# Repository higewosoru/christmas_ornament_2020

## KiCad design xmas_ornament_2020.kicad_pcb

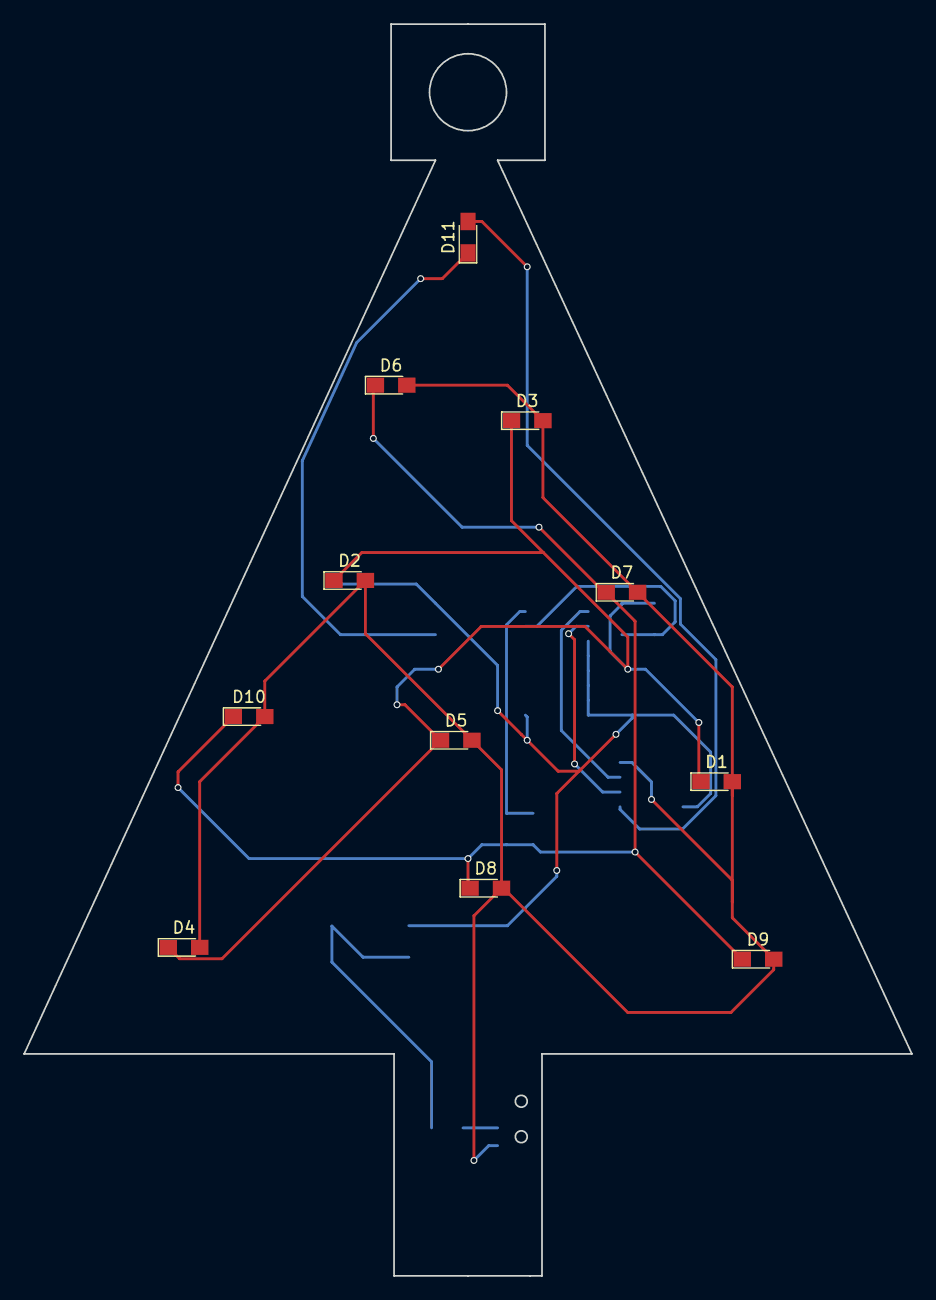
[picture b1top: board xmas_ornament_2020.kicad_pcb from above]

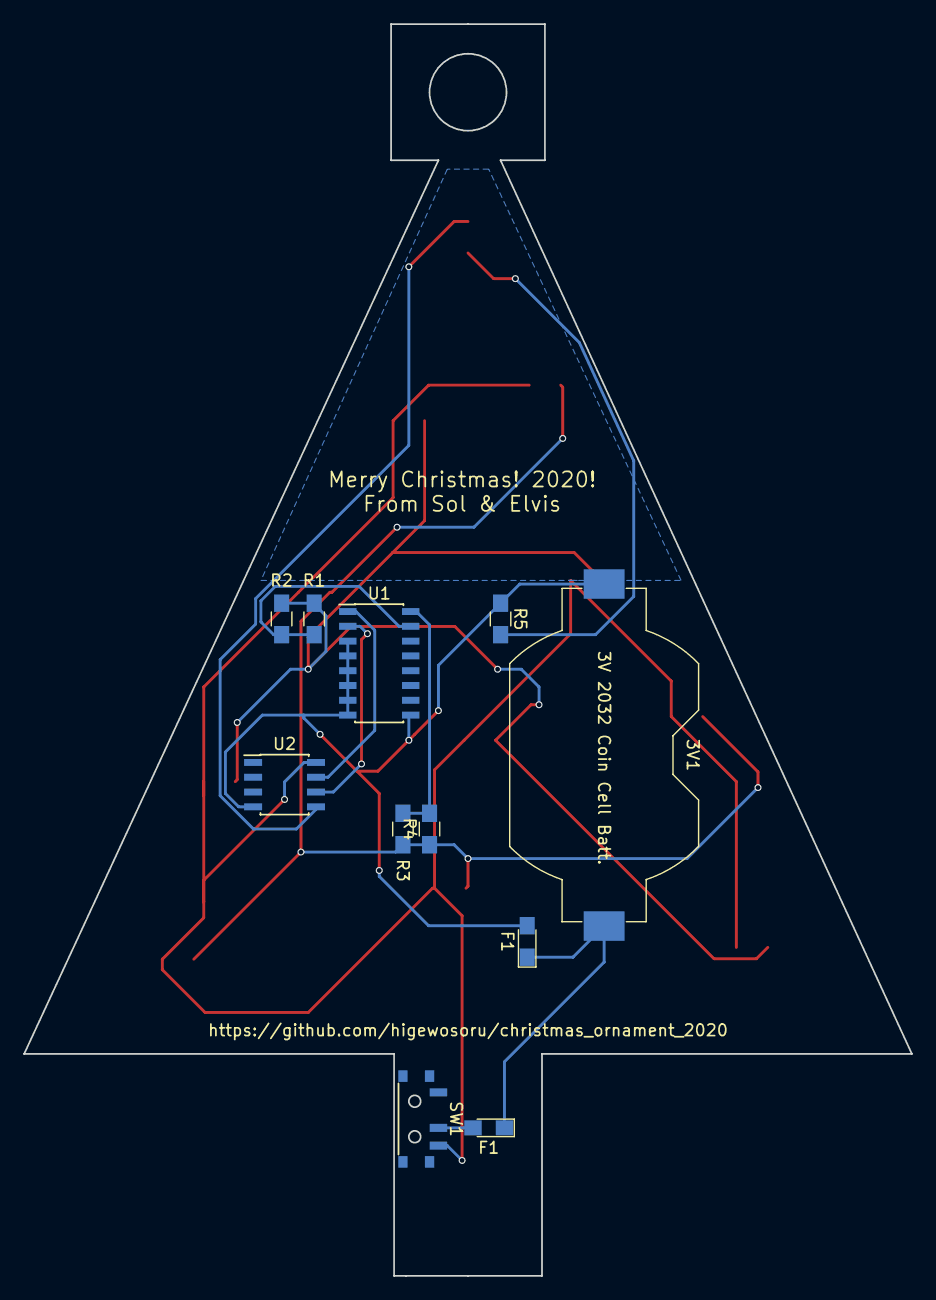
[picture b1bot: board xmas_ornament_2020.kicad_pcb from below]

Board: 2 copper layers, 76.2 x 107.4 mm, 22 parts (11 on the bottom side), 12 nets.

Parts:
3V1: Battery_Cell; Keystone_1058_1x2032-CoinCell
D1, D2, D3, D4, D5, D6, D7, D8, D9, D10: LED; LED_0805_HandSoldering
D11: TOP_LED; LED_0805_HandSoldering
F1, F1#2: 250mA; LED_0805_HandSoldering
R1, R2, R3, R4: 2K; R_0805_HandSoldering
R5: 1K; R_0805_HandSoldering
SW1: SW_SPDT; CUS-12B
U1: ULN2003A; SOIC-16_3.9x9.9mm_Pitch1.27mm
U2: ATTINY45-20SU; SOIC-8_3.9x4.9mm_Pitch1.27mm

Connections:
+3V3: D1.2, D2.2, D3.2, D4.2, D5.2, D6.2, D7.2, D8.2, D9.2, D10.2, SW1.3, U2.8
/group0: R3.2, R4.2, U1.16
/group1: R1.2, R2.2, U1.15
GND: 3V1.2, F1.2, R5.1, U1.3, U1.4, U1.5, U1.6, U1.7, U1.8, U1.9, U2.4
unnamed: 3V1.1, F1.1, F1#2.1
unnamed: D1.1, D2.1, D3.1, D4.1, D5.1, R1.1, R2.1
unnamed: D6.1, D7.1, D8.1, D9.1, D10.1, R3.1, R4.1
unnamed: D11.1, R5.2
unnamed: D11.2, U2.5
unnamed: F1#2.2, SW1.2
unnamed: U1.1, U2.7
unnamed: U1.2, U2.6

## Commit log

2020-11-26 layout done
2020-12-20 firmware untested
